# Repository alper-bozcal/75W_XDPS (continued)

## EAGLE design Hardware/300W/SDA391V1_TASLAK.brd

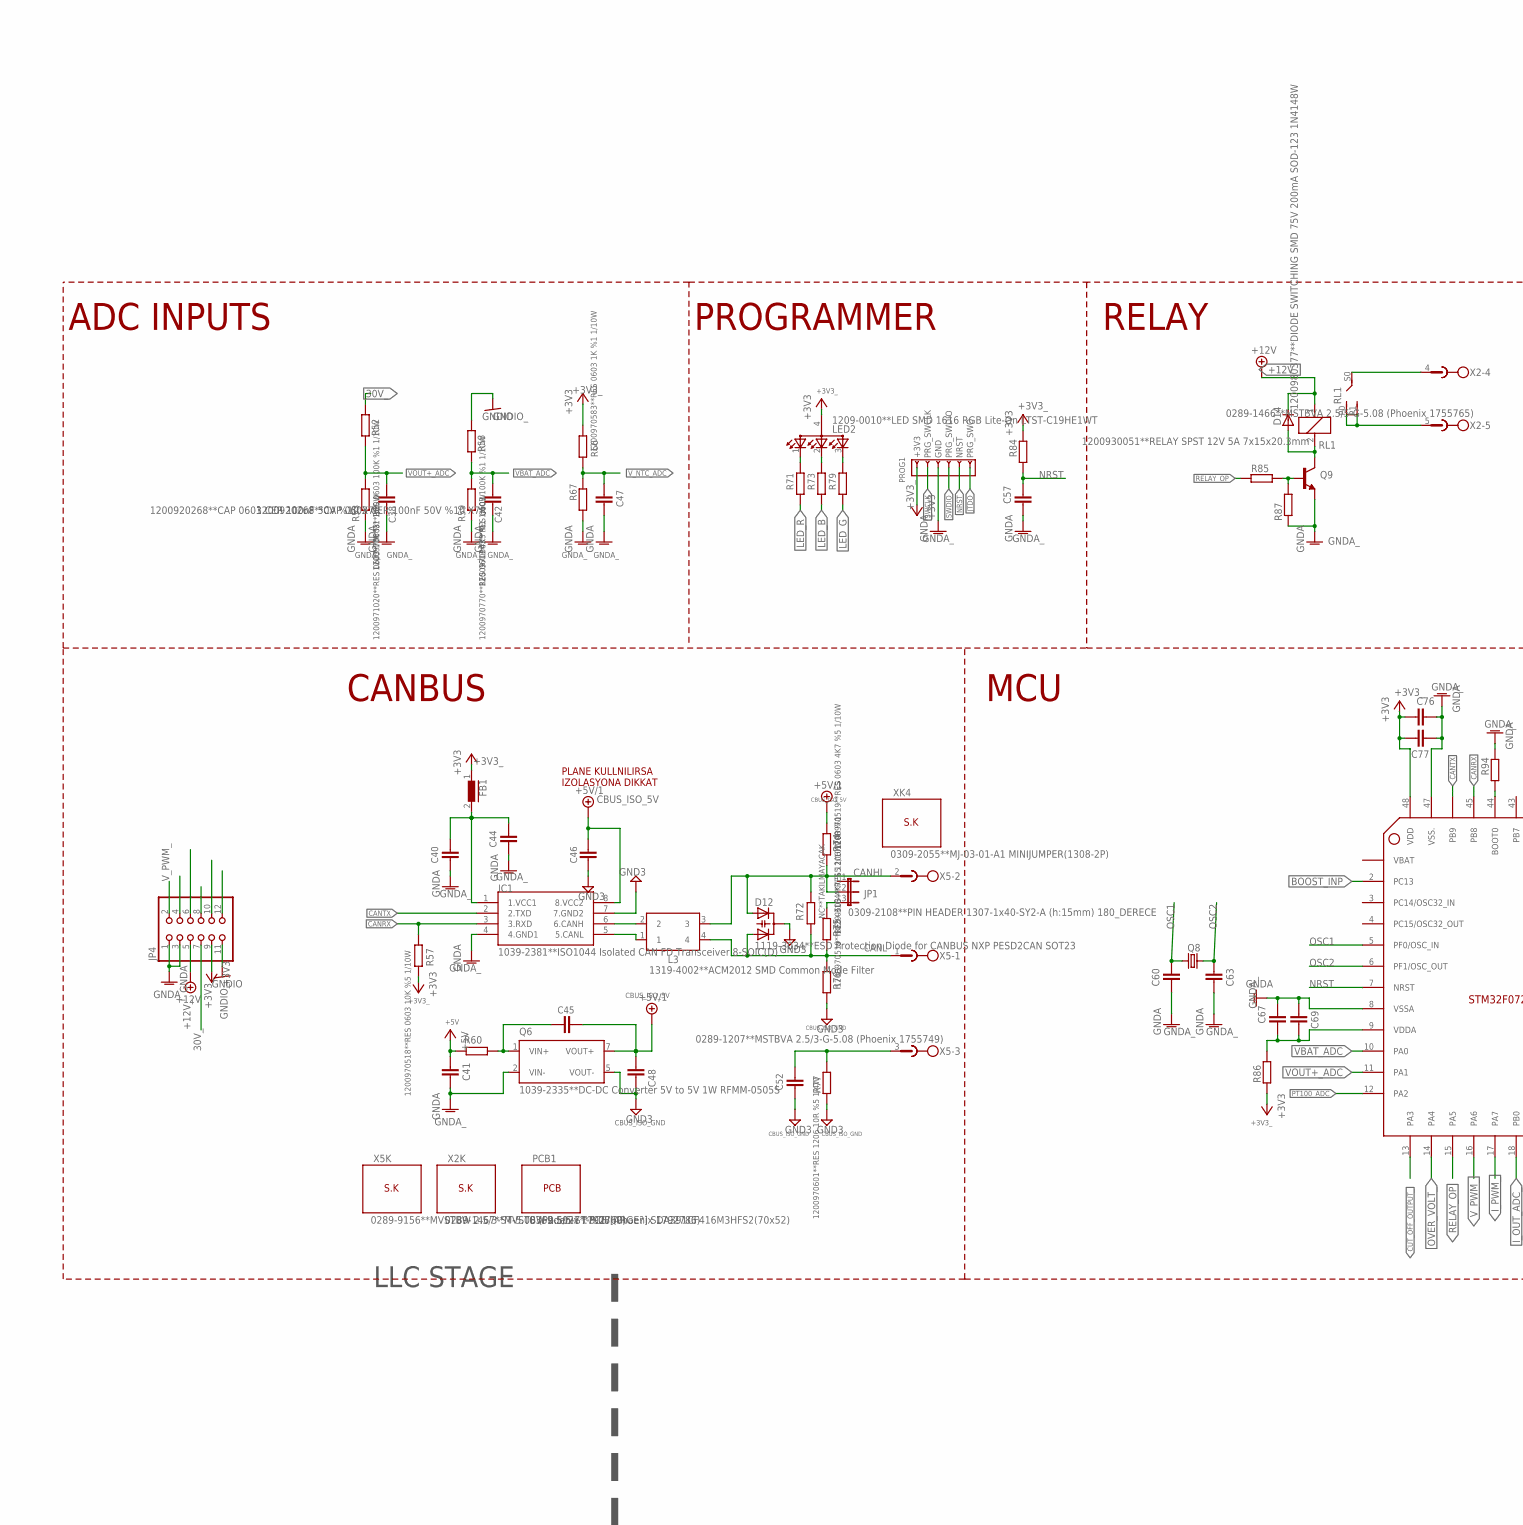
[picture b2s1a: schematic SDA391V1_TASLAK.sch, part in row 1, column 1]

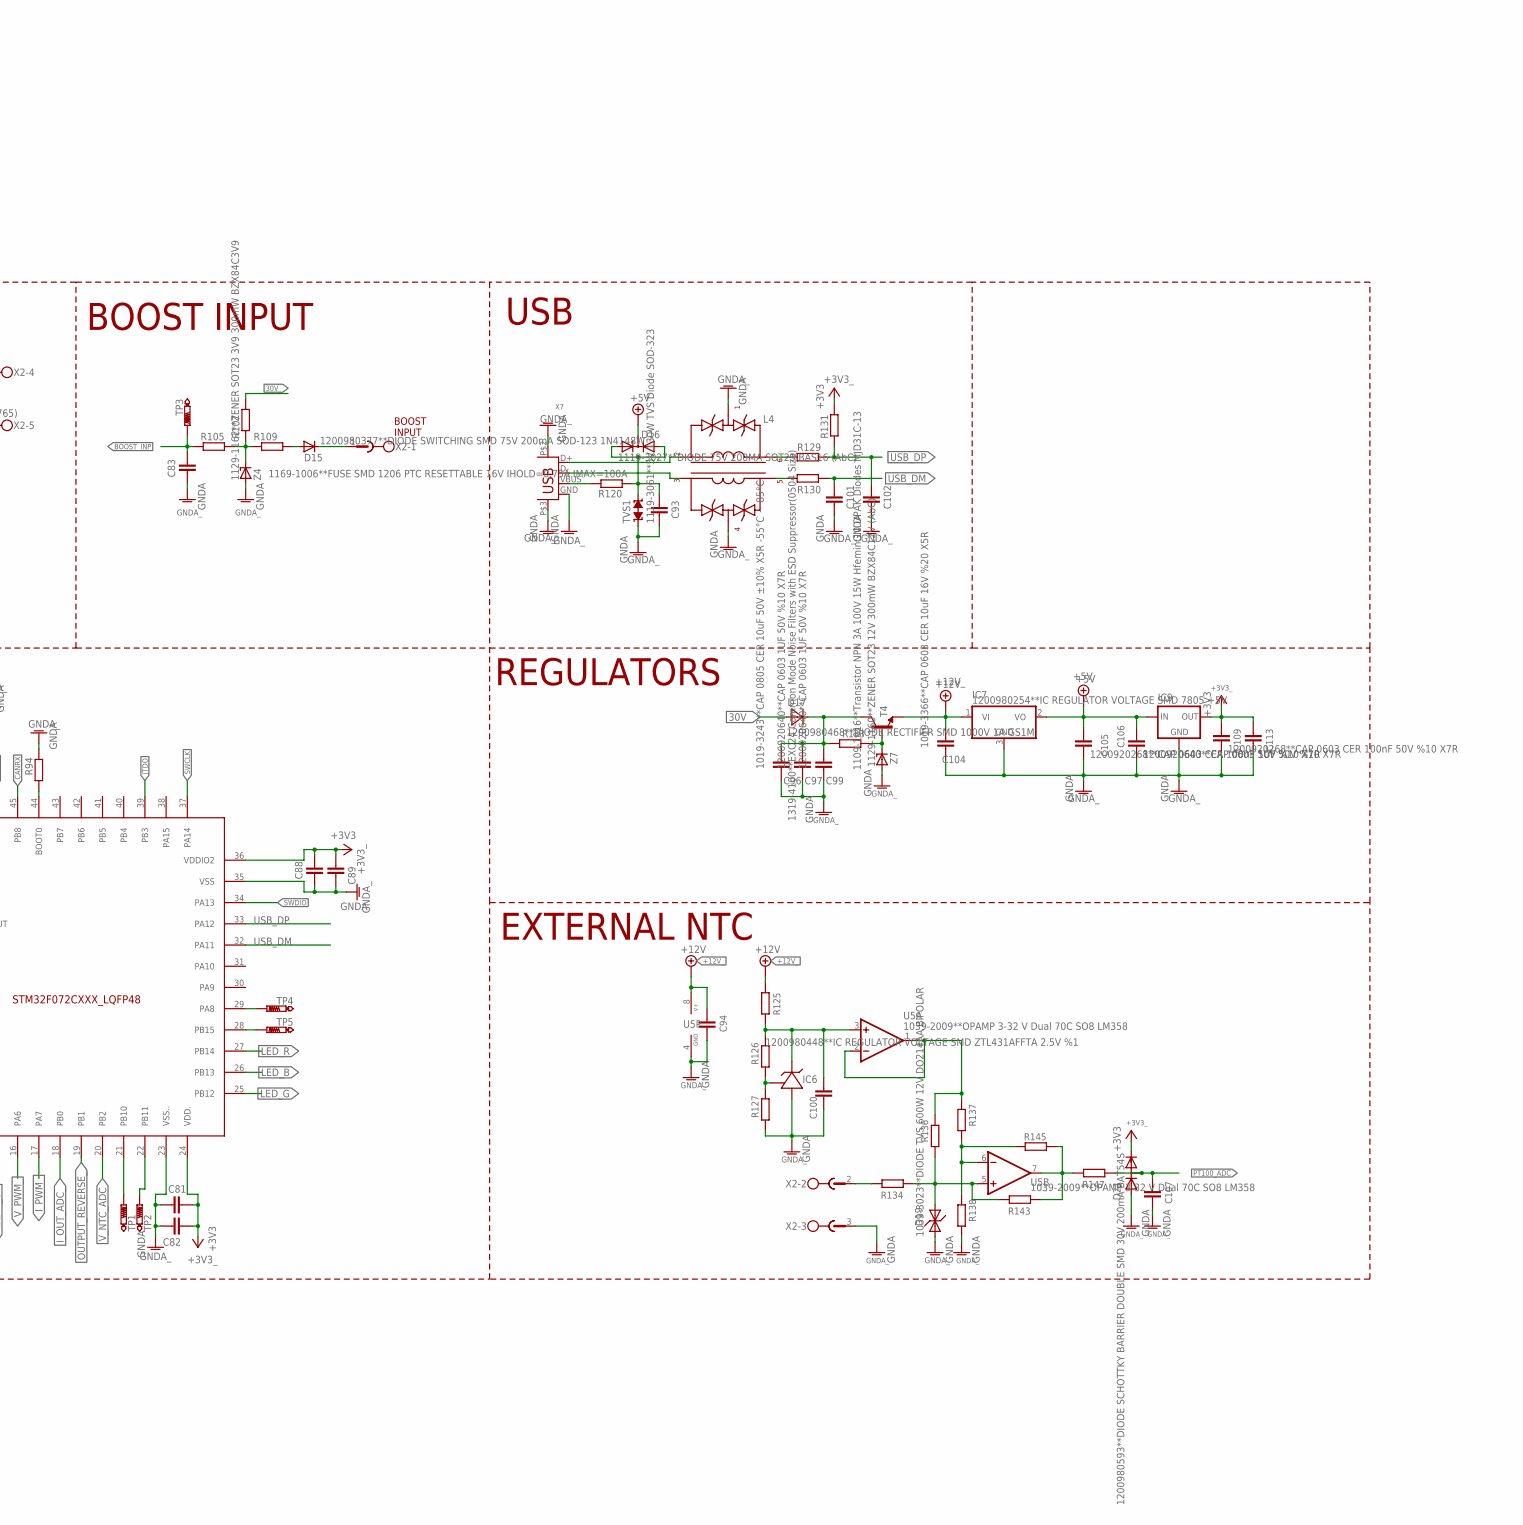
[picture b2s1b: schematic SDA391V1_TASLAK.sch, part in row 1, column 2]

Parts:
C38, C42, C44, C46, C47, C57, C67, C76, C82, C89, C93, C94, C100, C105, C107, C109: 1200920268**CAP 0603 CER 100nF 50V %10 X7R; C0603_ENKO
C40, C52: 1200920253**CAP 0603 CER 10n 50V%10 X7R; C0603_ENKO
C41, C48: 1019-3362**CAP 0603 CER 2.2uF 10V %10 X5R; C0603_ENKO
C45: 0019-3020**CAP TH CER 470pF 3kV Y5P %10 85C F=7.5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; C050-055X075_SMALL
C60, C63: 1019-3352**CAP 0603 CER 22pF 50V %5 NPO; C0603_ENKO
C69, C77, C81, C83, C88: 1019-3167**CAP 0603 CER 10nF 50V %10 X7R (AbC); C0603_ENKO
C96: 1019-3243**CAP 0805 CER 10uF 50V ±10% X5R -55°C ~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; C0805_ENKO
C97, C99, C106: 1200920640**CAP 0603 1UF 50V %10 X7R; C0603_ENKO
C101, C102: 1019-3381**CAP 0603 CER 33pf 50V %5 NPO(COG); C0603_ENKO
C104, C113: 1019-3366**CAP 0603 CER 10uF 16V %20 X5R; C0603_ENKO
D12: 1119-3034**ESD Protection Diode for CANBUS NXP PE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; SOT23
D14, D15: 1200980377**DIODE SWITCHING SMD 75V 200mA SOD-123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; SOD123
D16: 1119-3027**DIODE 75V 200MA SOT23 BAS16 (AbC); SOT23
D17: 1200980468**DIODE RECTIFIER SMD 1000V 1A GS1M; M7_DC_DIYOT
D19: 1039-3023**DIODE TVS 600W 12V DO214AA BIPOLAR; TRANSIL_SMB
D21: 1200980593**DIODE SCHOTTKY BARRIER DOUBLE SMD 30V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; SOT23
FB1: 1319-4060**Ferrite Bead SMD 0805 2kOhm@100MHz 300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; FERRITE_BEAT_0805
IC1: 1039-2381**ISO1044 Isolated CAN FD Transceiver 8-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; ISO1044
IC6: 1200980448**IC REGULATOR VOLTAGE SMD ZTL431AFFTA 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; TL431_SOT23F
IC7: 1200980254**IC REGULATOR VOLTAGE SMD 7805 +5V; TO252
IC9: 1039-3003**Voltage Regulator SOT-89 3.3V Diodes A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; SOT89
JP1: 0309-2108**PIN HEADER 1307-1x40-SY2-A (h:15mm) 18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; JP2
JP4: PINHD-2X6_2.54; 2X06
L3: 1319-4002**ACM2012 SMD Common Mode Filter; ACM2012-900--2P-T002
L4: 1319-4100**EXC24 Common Mode Noise Filters with E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; EXC24CS_COMMON_MODE
LED2: 1209-0010**LED SMD 1616 RGB Lite-On LTST-C19HE1WT; CCS3210_RGB_LED
PCB1: 0369-5027**PCB [ARGE?] SDA391CF416M3HFS2(70x52); PCB
PROG1: NC**TAKILMAYACAK; PROG_6PIN
Q6: 1039-2335**DC-DC Converter 5V to 5V 1W RFMM-0505S; RFMM-0505S
Q8: 1149-0006**HC49S SMD KRISTAL 8MHZ -40+85 20PF 50P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; HC49UP
Q9: 1200980090**TRANS SMD NPN BC847B SOT-23; SOT23
R52, R58: 1200970803**RES 0603 100K %1 1/10W; R0603_ENKO
R53: 1200971020**RES 0603 10K %1 1/10W; R0603_ENKO
R57, R84, R87, R105: 1200970518**RES 0603 10K %5 1/10W; R0603_ENKO
R59: 1200970770**RES 0603 4K3 %1 1/10W; R0603_ENKO
R60: 1319-4025**INDUCTOR SMD 0805 4.7uH 500mA CL2012C-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; R0805_ENKO
R66, R126, R138: 1200970583**RES 0603 1K %1 1/10W; R0603_ENKO
R67: 1169-1001**TSM2A103F3951RZ THINKING 0805 10K NTC 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; R0805_ENKO
R71, R73, R79: 1029-2005**RES 0603 220R %1; R0603_ENKO
R72: NC**TAKILMAYACAK; R1206_ENKO
R74, R76: 1200970519**RES 0603 4K7 %5 1/10W; R0603_ENKO
R75: 1029-3164**RES 1206 120R %1; R1206_ENKO
R77: 1200970601**RES 1206 10R %5 1/4W; R1206_ENKO
R85, R94: 1200970522**RES 0603 1K %5 1/10W; R0603_ENKO
R86: 1319-4060**Ferrite Bead SMD 0805 2kOhm@100MHz 300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; R0805_ENKO
R107: 1200970568**RES 0603 47K %5 1/10W; R0603_ENKO
R109: 1409-0025**RES 0603 470R %5 1/16W; R0603_ENKO
R120: 1169-1006**FUSE SMD 1206 PTC RESETTABLE 16V IHOLD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; R1206_ENKO
R125, R136: 1029-2234**RES 0603 4K7 %1; R0603_ENKO
R127: 1029-2231**RES 0603 1K8 %1; R0603_ENKO
R129, R130, R134: 1029-6086**RES 0603 22R %1; R0603_ENKO
R131: 1200970852**RES 0603 1K5 %5 1/10W; R0603_ENKO
R133: 1200970121**RES 0805 1K %5 1/8W; R0805_ENKO
R137: 1200970684**RES 0603 47K %1 1/10W; R0603_ENKO
R143: 1029-2229**RES 0603 120K %1; R0603_ENKO
R145: 1029-2219**RES 0603 30K %1; R0603_ENKO
R147: 1200970730**RES 0603 560R %1 1/10W; R0603_ENKO
RL1: 1200930051**RELAY SPST 12V 5A 7x15x20.3mm; ALD1_AND_ALJ_RELAY
T4: 1109-1016**Transistor NPN 3A 100V 15W Hfemin:10 D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; DPAK
TP1, TP2, TP3, TP4, TP5: PTR1TP20R; TP20R
TVS1: 1119-3061**5V 130W TVS Diode SOD-323; SOD323
U4: 1039-2220**STM32F072C8T6 64K Flash USB, CAN; STM32F072CXXX_LQFP48
U5: 1039-2009**OPAMP 3-32 V Dual 70C SO8 LM358; SO08
X2: 0289-1466**MSTBVA 2.5/5-G-5.08 (Phoenix 1755765); MSTBV5
X2K: 0289-1467**MVSTBW 2.5/5-ST-5.08 (Phoenix 1792786); SOKET
X5: 0289-1207**MSTBVA 2.5/3-G-5.08 (Phoenix 1755749); MSTBV3
X5K: 0289-9156**MVSTBW 2.5/3-ST-5.08 (Phoenix 1792760); SOKET
X7: 0309-1065**USB Type-B Mini Connector Vertical; USB-BV
XK4: 0309-2055**MJ-03-01-A1 MINIJUMPER(1308-2P); SOKET
Z4: 1129-1162**ZENER SOT23 3V9 300mW BZX84C3V9; SOT23
Z7: 1129-1160**ZENER SOT23 12V 300mW BZX84C12V (AbC); SOT23

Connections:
5.CANL: IC1.5 (5.CANL), L3.1
30V_: D17.A, JP4.7, R52.1, R107.1
+3V3_: C76.1, C77.1, C81.1, C82.1, C88.1, C89.1, C109.1, C113.1, D21.2 (C), FB1.1, IC9.3 (OUT), JP4.9, LED2.4, PROG1.1 (+3V3), R57.2, R66.2, R84.1, R86.2, R131.2, U4.24 (VDD.), U4.36 (VDDIO2), U4.48 (VDD)
+5V: C41.1, C105.1, C106.1, D16.3 (C), IC7.2 (VO), IC9.2 (IN), R60.1
+12V_: C94.1, C104.1, D14.C, IC7.1 (VI), JP4.5, R125.2, RL1.1, T4.3 (E), U5.8 (V+)
BOOST_INP: C83.1, R105.1, TP3.TP, U4.2 (PC13)
CANHI: D12.1 (A1), JP1.2, L3.3, R72.2, R74.1, X5.2
CANL: D12.2 (A2), L3.4, R72.1, R75.1, R76.2, X5.1
CANRX: IC1.3 (3.RXD), R57.1, U4.45 (PB8)
CANTX: IC1.2 (2.TXD), U4.46 (PB9)
CBUS_ISO_5V: C45.2, C46.2, C48.1, IC1.8 (8.VCC2), Q6.7 (VOUT+), R74.2
CBUS_ISO_GND: C48.2, C52.2, IC1.7 (7.GND2), Q6.5 (VOUT-), R76.1, R77.2
CUT_OFF_OUTPUT_: JP4.6, U4.13 (PA3)
GND3: C46.1, D12.3 (C)
GNDA_: C38.2, C40.1, C41.2, C42.2, C44.1, C47.2, C57.1, C60.2, C63.2, C67.2, C69.2, C76.2, C77.2, C81.2, C82.2, C83.2, C88.2, C89.2, C93.2, C94.2, C96.2, C97.2, C99.2, C100.1, C101.2, C102.2, C104.2, C105.2, C106.2, C107.1, C109.2, C113.2, D19.A1, D21.1 (A), IC1.4 (4.GND1), IC6.A (1), IC7.3 (GND), IC9.1 (GND), JP4.1, JP4.3, L4.1 (1.GND), L4.4 (4.GND), PROG1.3 (GND), Q6.2 (VIN-), Q9.2 (E), R53.2, R59.2, R67.2, R87.1, R94.1, R127.1, R138.1, TVS1.A (1), U4.8 (VSSA), U4.23 (VSS..), U4.35 (VSS), U4.47 (VSS.), U5.4 (GND), X2.3, X7.GND, X7.P$2 (1), X7.P$3 (2), Z4.1 (A), Z7.1 (A)
GNDIO_: JP4.11, R58.1
I_OUT_ADC_: JP4.10, U4.18 (PB0)
I_PWM_: JP4.4, U4.17 (PA7)
JTDO: PROG1.6 (PRG_SWO), U4.39 (PB3)
LED_B: R73.1, U4.26 (PB13)
LED_G: R79.1, U4.25 (PB12)
LED_R: R71.1, U4.27 (PB14)
unnamed: L4.6, R129.1
unnamed: LED2.1, R71.2
unnamed: R105.2, R107.2, R109.2, Z4.3 (C)
unnamed: D15.A, R109.1
unnamed: D15.C, X2.1
unnamed: IC6.R (2), R126.1, R127.2
unnamed: R134.1, X2.2
unnamed: TP1.TP, U4.21 (PB10)
unnamed: R94.2, U4.44 (BOOT0)
unnamed: TP2.TP, U4.22 (PB11)
unnamed: TP5.TP, U4.28 (PB15)
unnamed: TP4.TP, U4.29 (PA8)
unnamed: C52.1, R77.1, X5.3
unnamed: JP1.3, R75.2
unnamed: IC1.6 (6.CANH), L3.2
unnamed: C45.1, Q6.1 (VIN+), R60.2
unnamed: C67.1, C69.1, R86.1, U4.9 (VDDA)
unnamed: LED2.2, R73.2
unnamed: LED2.3, R79.2
unnamed: R137.1, R138.2, R145.1, U5.6 (-IN)
unnamed: D19.A, R134.2, R136.1, R143.1, U5.5 (+IN)
unnamed: R143.2, R145.2, R147.1, U5.7 (OUT)
unnamed: D14.A, Q9.3 (C), RL1.2
unnamed: Q9.1 (B), R85.1, R87.2
unnamed: L4.5, R130.1
unnamed: C100.2, IC6.C (3), R125.1, R126.2, U5.3 (+IN)
unnamed: R136.2, R137.2, U5.1 (OUT), U5.2 (-IN)
unnamed: R133.1, T4.1 (B), Z7.3 (C)
unnamed: C96.1, C97.1, C99.1, D17.C, R133.2, T4.4 (C)
unnamed: L4.3, X7.D-
unnamed: L4.2, X7.D+
unnamed: C93.1, D16.1 (A1), D16.2 (A2), R120.1, TVS1.C (2)
unnamed: C40.2, C44.2, FB1.2, IC1.1 (1.VCC1)
NRST: C57.2, PROG1.5 (NRST), R84.2, U4.7 (NRST)
OSC1: C60.1, Q8.1, U4.5 (PF0/OSC_IN)
OSC2: C63.1, Q8.2, U4.6 (PF1/OSC_OUT)
OUTPUT_REVERSE_: JP4.12, U4.19 (PB1)
OVER_VOLT_: JP4.8, U4.14 (PA4)
PT100_ADC: C107.2, D21.3 (AC), R147.2, U4.12 (PA2)
RELAY_OP: R85.2, U4.15 (PA5)
RL+: RL1.P0, RL1.P1, X2.5
RL-: RL1.S0, X2.4
SWCLK: PROG1.2 (PRG_SWCLK), U4.37 (PA14)
SWDIO: PROG1.4 (PRG_SWDIO), U4.34 (PA13)
USB_DM: C101.1, R130.2, U4.32 (PA11)
USB_DP: C102.1, R129.2, R131.1, U4.33 (PA12)
VBAT_ADC: C42.1, R58.2, R59.1, U4.10 (PA0)
VBUS1: R120.2, X7.VBUS
VOUT+_ADC: C38.1, R52.2, R53.1, U4.11 (PA1)
V_NTC_ADC: C47.1, R66.1, R67.1, U4.20 (PB2)
V_PWM_: JP4.2, U4.16 (PA6)

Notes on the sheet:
LLC STAGE
AUXILIARY VOLTAGE REGULATOR
STM32G030F6P6
ISOLATION BARRIER
ISOLATED CONVERTER
BOOST INPUT
CANBUS
PLANE KULLNILIRSA IZOLASYONA DIKKAT
MCU
REGULATORS
EXTERNAL NTC
USB
BOOST INPUT
RELAY
PROGRAMMER
ADC INPUTS

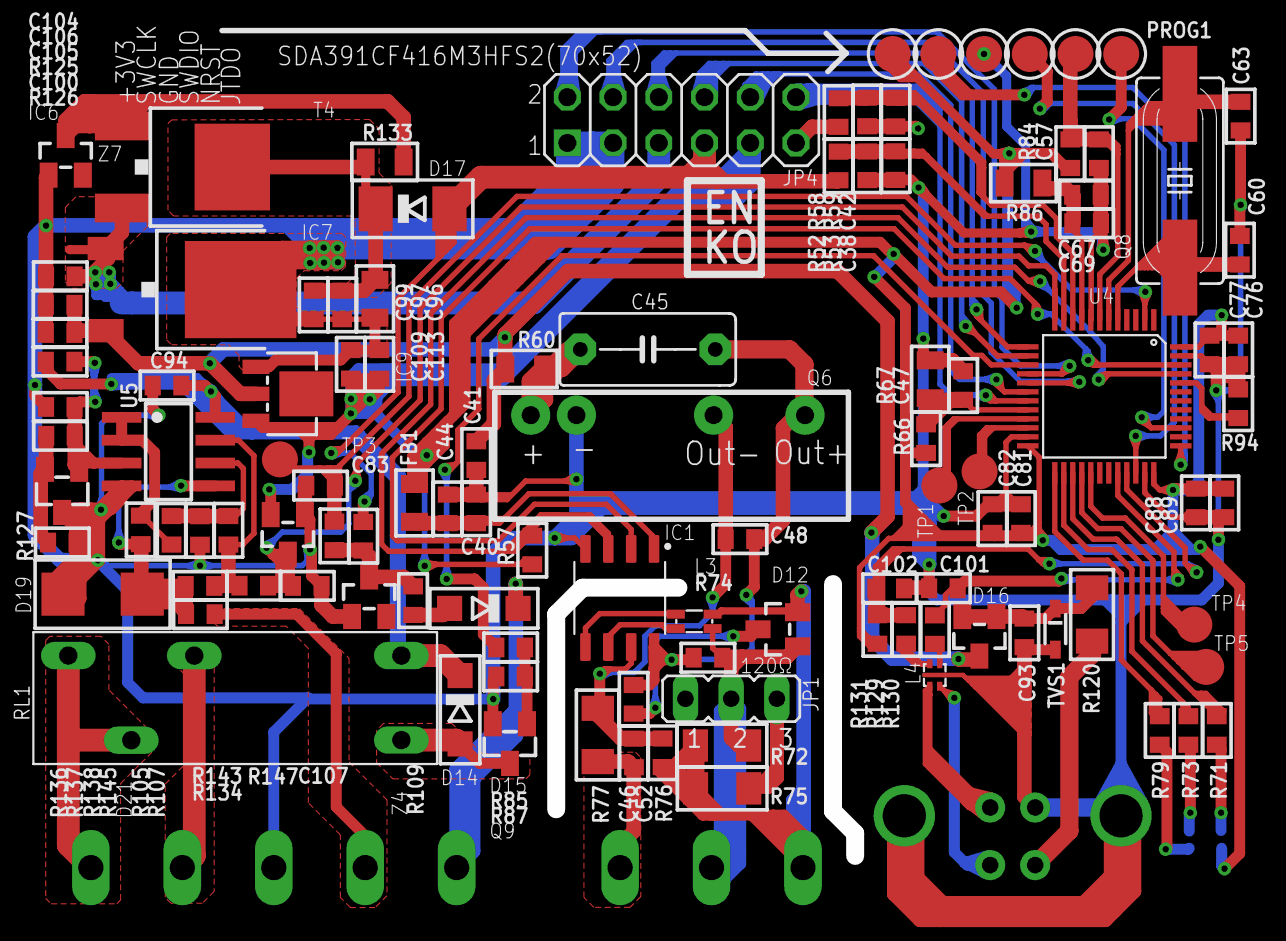
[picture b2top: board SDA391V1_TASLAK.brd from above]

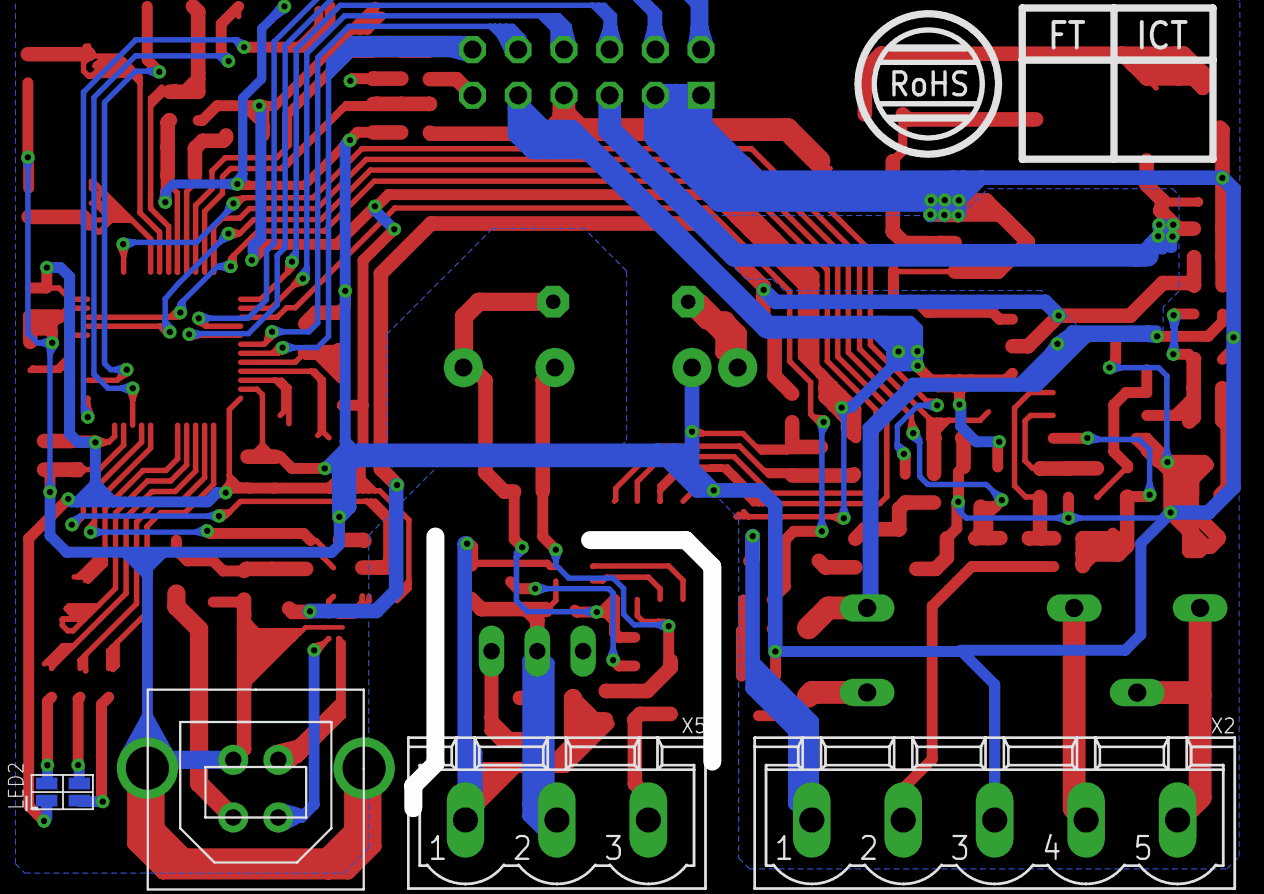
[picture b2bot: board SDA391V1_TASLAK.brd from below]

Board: 3 copper layers, 118 parts (6 on the bottom side), 73 nets.

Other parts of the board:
U$1: EN-KO_AMLEMI
U$2: ROHS
U$3: FT-ICT
